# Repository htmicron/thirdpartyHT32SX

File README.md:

# Third-party HT32SX contributions

Third party contributions to HT32SX (https://github.com/htmicron/ht32sx)

* Kicad footprint for ht32sx [here](./kicad)
* Devkit for ht32sx version 2.2 [here](./devkit)

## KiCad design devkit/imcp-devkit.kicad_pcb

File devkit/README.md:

# DEVKIT FOR HT32SX version 2.2

Original repository: [here](https://github.com/disk91/HTMICRON-iMCP-devkit)

Log:
* Original files copied.

<hr>

# Devkit for HTMicron iMCP / stm32-s2lp / Sigfox SiP

This is a simple devkit board for the iMCP chip from HTMicron.
The current status is:
- Waiting for the first PCB samples. As a consequence the presence of design bug is 100% possible.

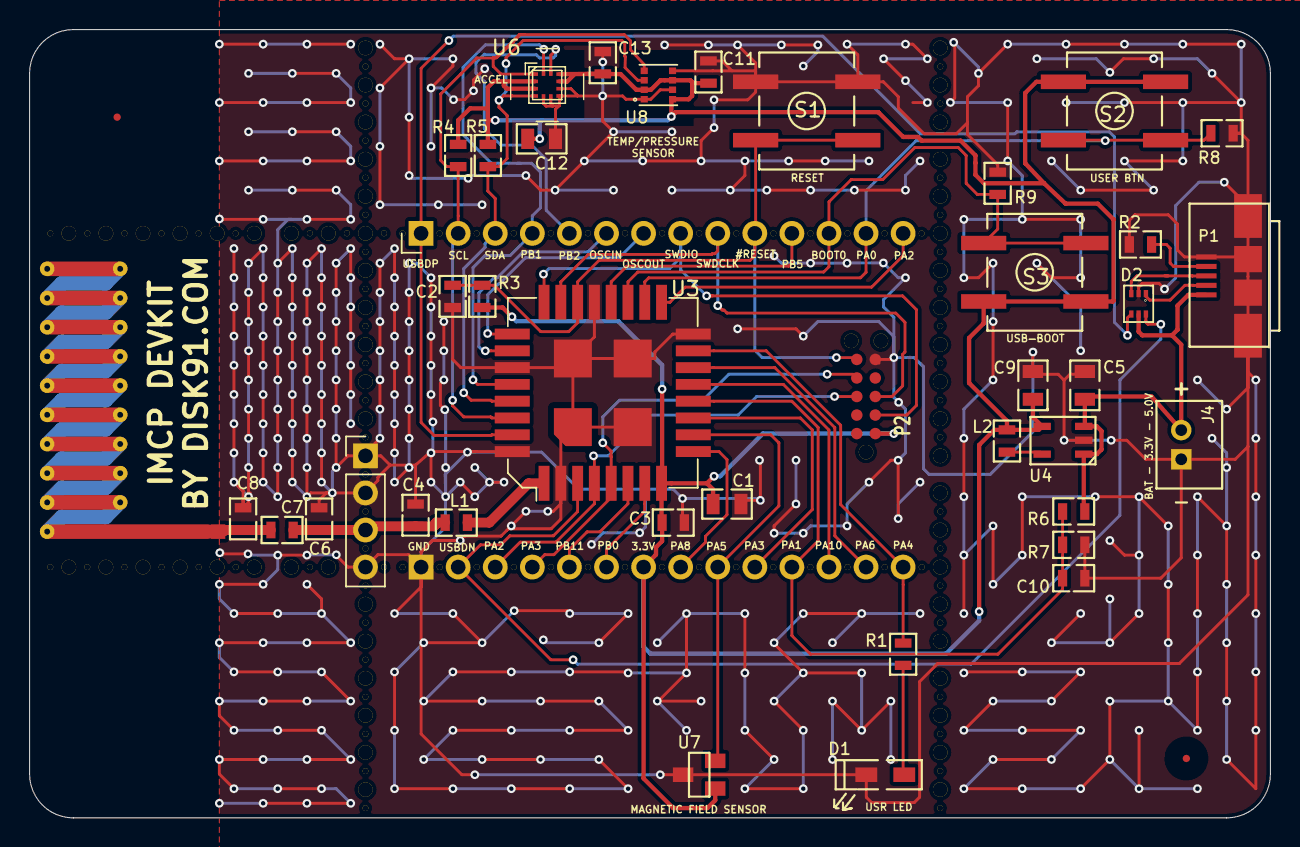
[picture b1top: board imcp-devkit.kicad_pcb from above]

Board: 2 copper layers, 85.0 x 54.0 mm, 43 parts (0 on the bottom side), 37 nets.

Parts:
C1, C5, C9, C12: 10uF; dsk-SM0805
C2: 1uF; dsk-SM0603
C3, C11, C13: 0,1uF; dsk-SM0603
C4: 4.7pF; dsk-SM0603
C6, C7, C8: C; dsk-SM0603
C10: 0.1uF; dsk-SM0603
D1: LED; dsk-Edge-Led-cms-2mm
D2: WE-TVS_82400152; dsk-imp-wurth-tvs-usb-82400152-WE-TVS_SOT563
J1, J3: Conn_01x14; dsk-conn-1x14_P2.54mm_Vertical
J2: Conn_01x04; dsk-conn-1x04-p2.54-Vertical
J4: Conn_01x02; dsk-cnx-jstx2-2mm
L1: 5,6nH; dsk-SM0603
L2: 10uH; dsk-SM0603
P1: MICRO-USB-B; dsk-usb-micro
P2: TC-2050; TC2050_IDC
R1: 1K; dsk-SM0603
R2, R3, R4, R5, R8, R9: 10K; dsk-SM0603
R6, R7: 2M; dsk-SM0603
S1, S2, S3: Switch_Wurth-434153017835; dsk-switch-univ
U1, U2: fiducial-global; dsk-fiducial
U3: iMCP_HT32SX_2_2; iMCP_HT32SX
U4: LM3670; dsk-SOT23A-CMPLIPO
U5: ANTENNA_SMPL; dsk-ant-Texas_SWRA416_868MHz_915MHz
U6: LIS2DH12; dsk-lis2dh-lga12
U7: SI7201-b-06-iv; dsk-diode-SOT23
U8: BME280; dsk-imp-bme280

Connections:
+5V: C5.2, D2.5, J4.2, P1.1, R6.1, U4.1, U4.3
/Ant0: L1.2, U3.1
/Ant2: C7.1, C8.2, U5.1
ANT1: C4.2, C6.2, C7.2, J2.3, L1.1
BOOT0: J1.12, R9.2, S3.2, S3.4, U3.19
DN: D2.1, P1.2
DP: D2.3, P1.3
GND: C1.1, C2.1, C3.1, C4.1, C5.1, C6.1, C8.1, C9.2, C10.2, C11.2, C12.1, C13.2, D1.2, D2.2, J2.1, J2.2, J2.4, J3.1, J4.1, P1.5, P1.6, P1.7, P1.8, P1.9, P2.5, R2.1, R7.1, R8.1, R9.1, S1.2, S1.4, U3.2, U3.16, U3.21, U3.27, U3.32, U3.33, U4.2, U6.5, U6.6, U6.7, U6.8, U7.3, U8.1, U8.5, U8.7
NRESET: C2.2, J1.10, P2.6, R3.1, S1.1, S1.3, U3.22
unnamed: D1.1, R1.1
unnamed: L2.2, U4.5
unnamed: P1.4, R2.2
OSC_IN: J1.6, U3.26
OSC_OUT: J1.7, U3.25
PA0: J1.13, R8.2, S2.2, S2.4, U3.18
PA1: C10.1, J3.11, R6.2, R7.2, U3.12
PA2: J1.14, U3.17
PA3: J3.10, U3.11
PA4: J3.14, R1.2, U3.15
PA5: J3.9, U3.10, U7.2
PA6: J3.13, U3.14
PA8: J3.8, U3.9
PB0: J3.6, U3.7
PB1: J1.4, U3.28, U6.12
PB2: J1.5, U6.11
PB5: J1.11, U3.20
PB10: J3.12, U3.13
PB11: J3.5, U3.6
RX: J3.4, P2.7, U3.5
SCL: J1.2, R4.2, U3.30, U6.1, U8.4
SDA: J1.3, R5.2, U3.29, U6.4, U8.3
SWDCLK: J1.9, P2.3, U3.23
SWDIO: J1.8, P2.2, U3.24
TX: J3.3, P2.8, U3.4
USBDN: D2.6, J3.2, U3.3
USBDP: D2.4, J1.1, U3.31
VCC: C1.2, C3.2, C9.1, C11.1, C12.2, C13.1, J3.7, L2.1, P2.1, R3.2, R4.1, R5.1, S2.1, S2.3, S3.1, S3.3, U3.8, U4.4, U6.2, U6.3, U6.9, U6.10, U7.1, U8.2, U8.6, U8.8

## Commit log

2020-07-01 kicad footprint
2020-07-01 kicad footprint patched
2020-07-01 fix readme
2020-07-02 add devkit
